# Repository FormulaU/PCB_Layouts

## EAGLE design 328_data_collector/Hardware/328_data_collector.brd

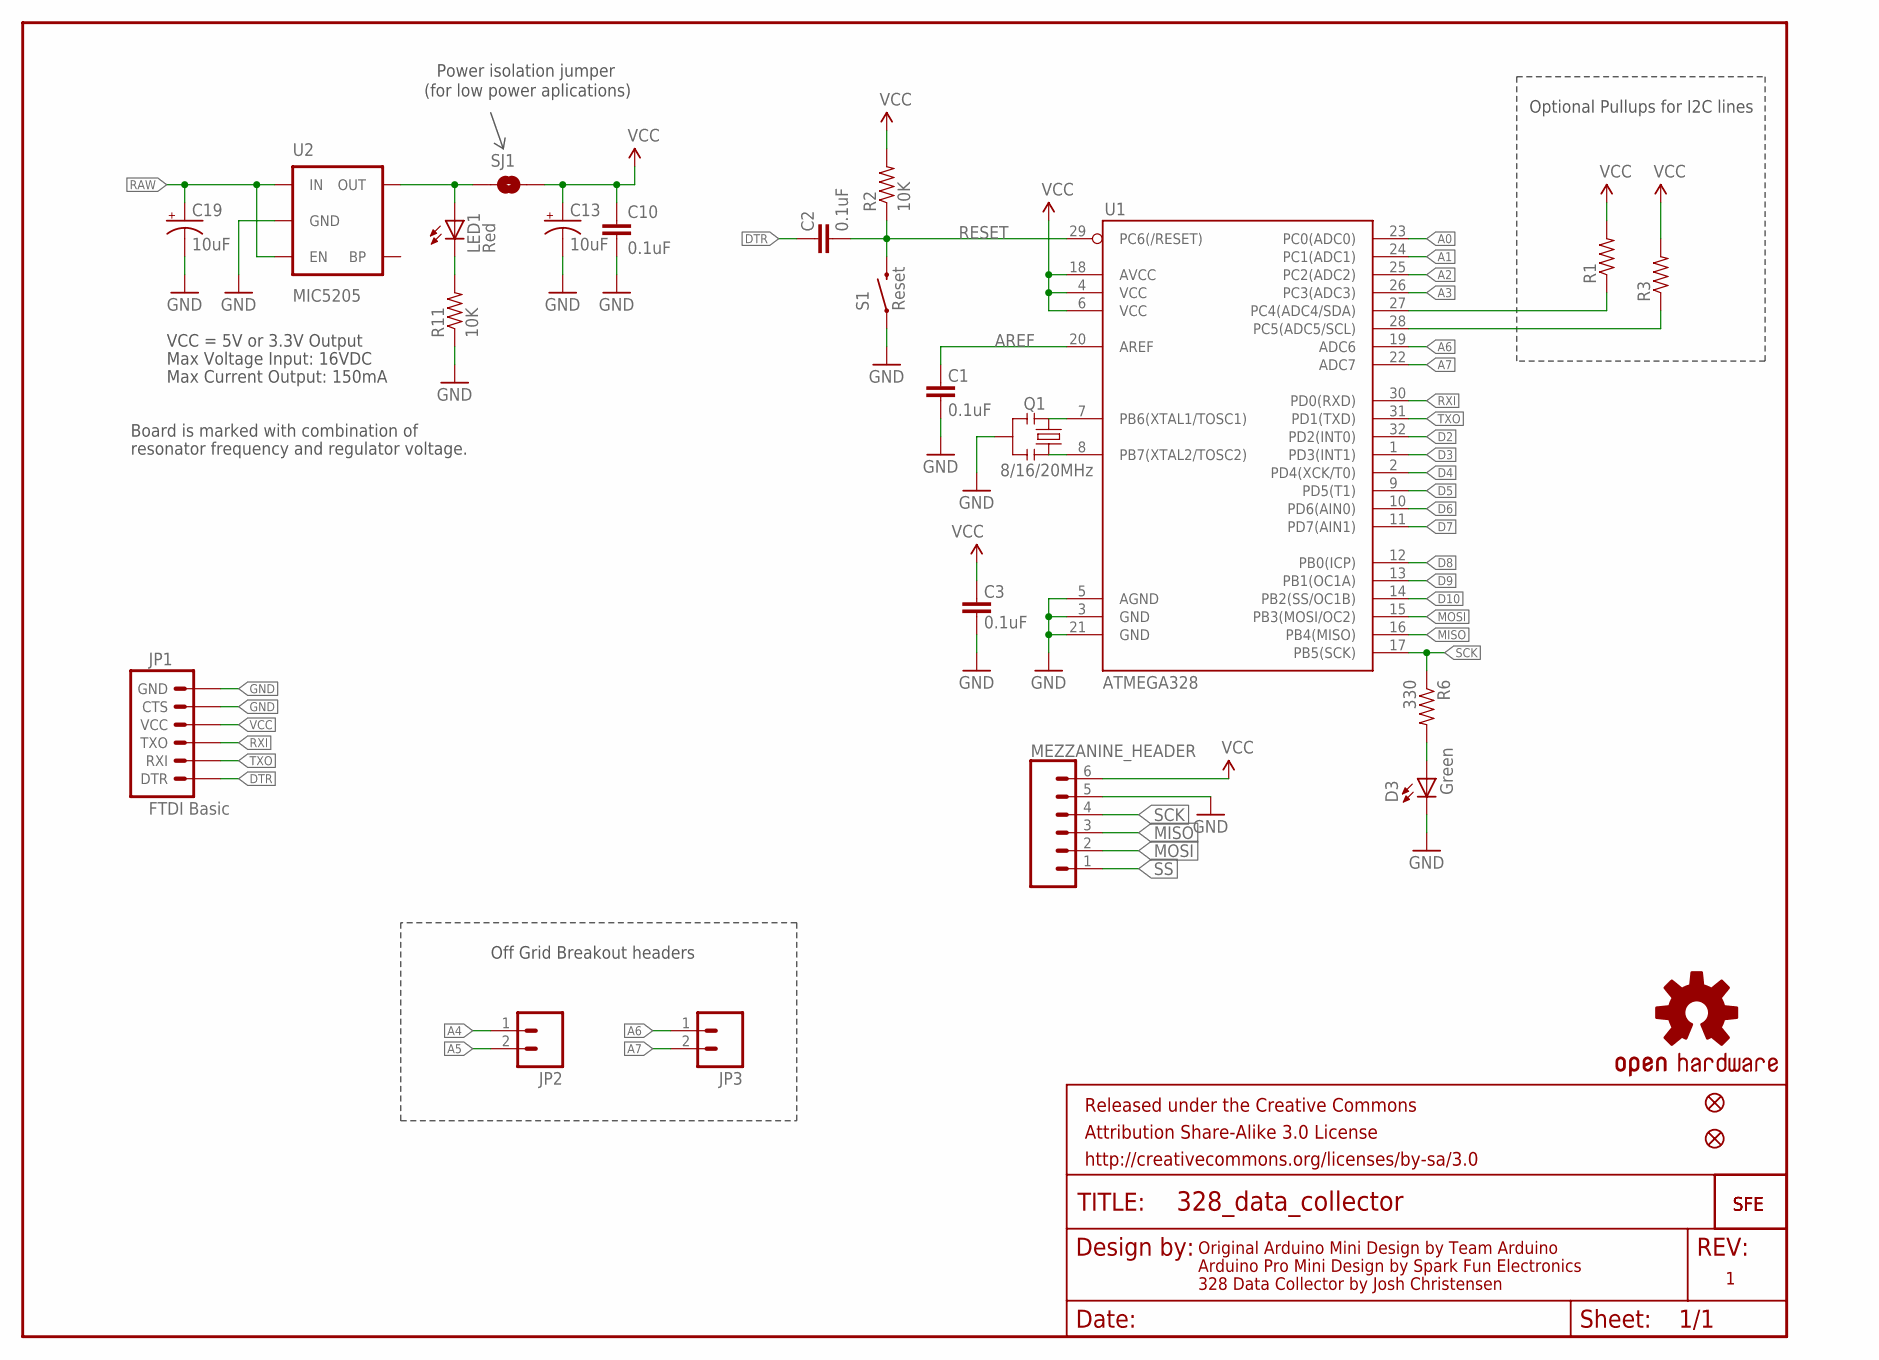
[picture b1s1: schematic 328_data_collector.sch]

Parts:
C1, C2, C3, C10: 0.1uF; 0603-CAP
C13, C19: 10uF; EIA3216
D3: Green; 0603-LED-ALT1
FRAME1: FRAME-LETTER; CREATIVE_COMMONS
JP1: FTDI Basic; 1X06
JP2, JP3: M02PTH; 1X02
JP5, JP8: FIDUCIALUFIDUCIAL; MICRO-FIDUCIAL
LED1: Red; 0603-LED-ALT1
MEZZANINE_HEADER: CONN_06SILK_FEMALE_PTH; 1X06
Q1: 8/16/20MHz; RESONATOR-SMD-1:1
R1, R3: RESISTOR0603-RES; 0603-RES
R2, R11: 10K; 0603-RES
R6: 330; 0603-RES
S1: Reset; TACTILE-SWITCH-SMD-ALT01
SJ1: SOLDERJUMPERNC; SJ_2S
U1: ATMEGA328; TQFP32-08
U2: MIC5205; SOT23-5
U$1: LOGO-SFESK; SFE-LOGO-FLAME
U$3: OSHW-LOGOS; OSHW-LOGO-S
U$11: LOGO-SFENEW; SFE-NEW-WEBLOGO

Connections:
3.3V: MEZZANINE_HEADER.6
A0: U1.23 (PC0(ADC0))
A1: U1.24 (PC1(ADC1))
A2: U1.25 (PC2(ADC2))
A3: U1.26 (PC3(ADC3))
A4: JP2.1, R1.1, U1.27 (PC4(ADC4/SDA))
A5: JP2.2, R3.1, U1.28 (PC5(ADC5/SCL))
A6: JP3.1, U1.19 (ADC6)
A7: JP3.2, U1.22 (ADC7)
AREF: C1.2, U1.20 (AREF)
D2: U1.32 (PD2(INT0))
D3: U1.1 (PD3(INT1))
D4: U1.2 (PD4(XCK/T0))
D5: U1.9 (PD5(T1))
D6: U1.10 (PD6(AIN0))
D7: U1.11 (PD7(AIN1))
D8: U1.12 (PB0(ICP))
D9: U1.13 (PB1(OC1A))
D10: U1.14 (PB2(SS/OC1B))
DTR: C2.2, JP1.1 (DTR)
GND: C1.1, C3.1, C10.2, C13.C (-), C19.C (-), D3.C, JP1.5 (CTS), JP1.6 (GND), MEZZANINE_HEADER.5, Q1.2, R11.1, S1.1, S1.2 (1), U1.3 (GND), U1.5 (AGND), U1.21 (GND), U2.2 (GND)
MISO: MEZZANINE_HEADER.3, U1.16 (PB4(MISO))
MOSI: MEZZANINE_HEADER.2, U1.15 (PB3(MOSI/OC2))
unnamed: Q1.3, U1.8 (PB7(XTAL2/TOSC2))
unnamed: Q1.1, U1.7 (PB6(XTAL1/TOSC1))
unnamed: LED1.A, SJ1.1, U2.5 (OUT)
unnamed: LED1.C, R11.2
unnamed: D3.A, R6.2
RAW: C19.A (+), U2.1 (IN), U2.3 (EN)
RESET: C2.1, R2.1, S1.3 (2), S1.4 (2), U1.29 (PC6(/RESET))
RXI: JP1.3 (TXO), U1.30 (PD0(RXD))
SCK: MEZZANINE_HEADER.4, R6.1, U1.17 (PB5(SCK))
SS: MEZZANINE_HEADER.1
TXO: JP1.2 (RXI), U1.31 (PD1(TXD))
VCC: C3.2, C10.1, C13.A (+), JP1.4 (VCC), R1.2, R2.2, R3.2, SJ1.2, U1.4 (VCC), U1.6 (VCC), U1.18 (AVCC)

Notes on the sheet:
Original Arduino Mini Design by Team Arduino
Arduino Pro Mini Design by Spark Fun Electronics
Max Voltage Input: 16VDC
Max Current Output: 150mA
Board is marked with combination of
resonator frequency and regulator voltage.
VCC = 5V or 3.3V Output
Optional Pullups for I2C lines
Off Grid Breakout headers
Power isolation jumper
(for low power aplications)
328 Data Collector by Josh Christensen

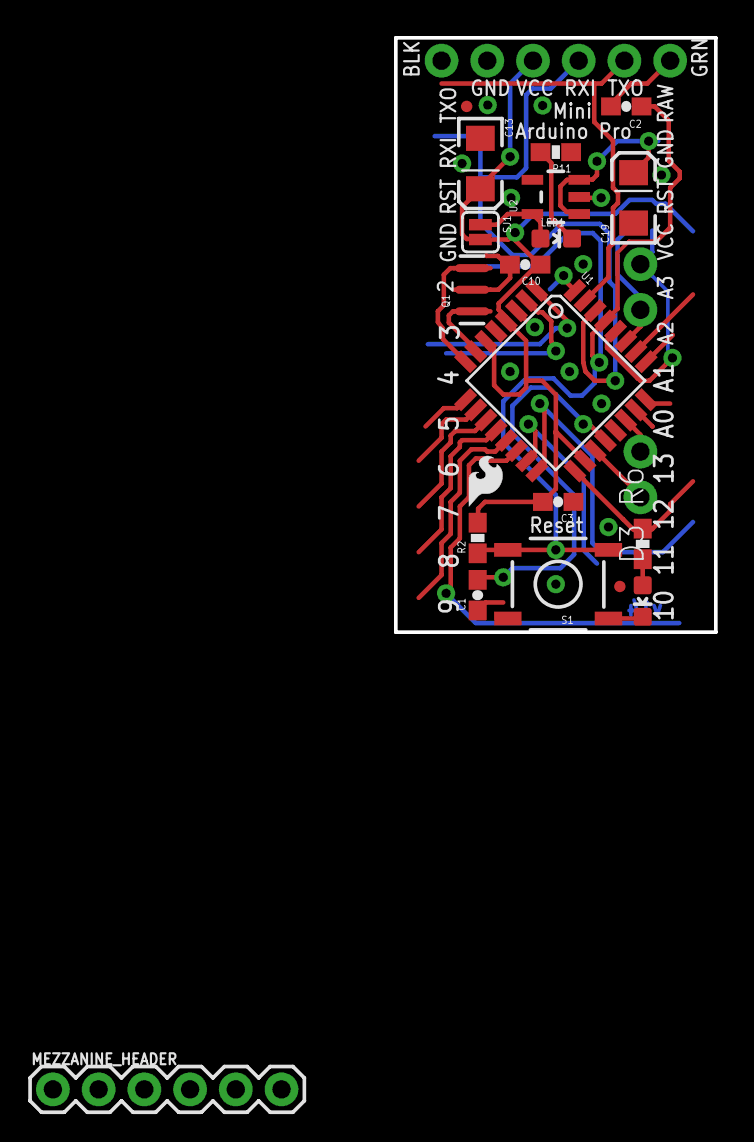
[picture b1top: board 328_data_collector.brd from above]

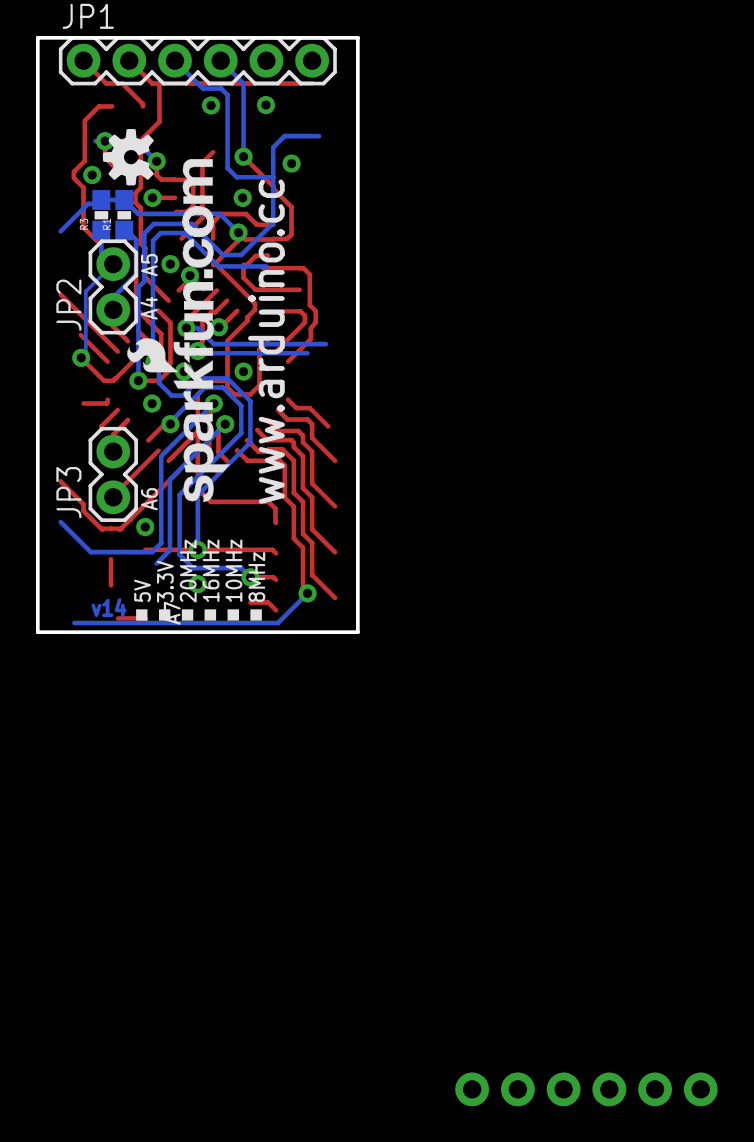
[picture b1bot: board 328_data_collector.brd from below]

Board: 2 copper layers, 17.8 x 33.0 mm, 28 parts (7 on the bottom side), 20 nets.

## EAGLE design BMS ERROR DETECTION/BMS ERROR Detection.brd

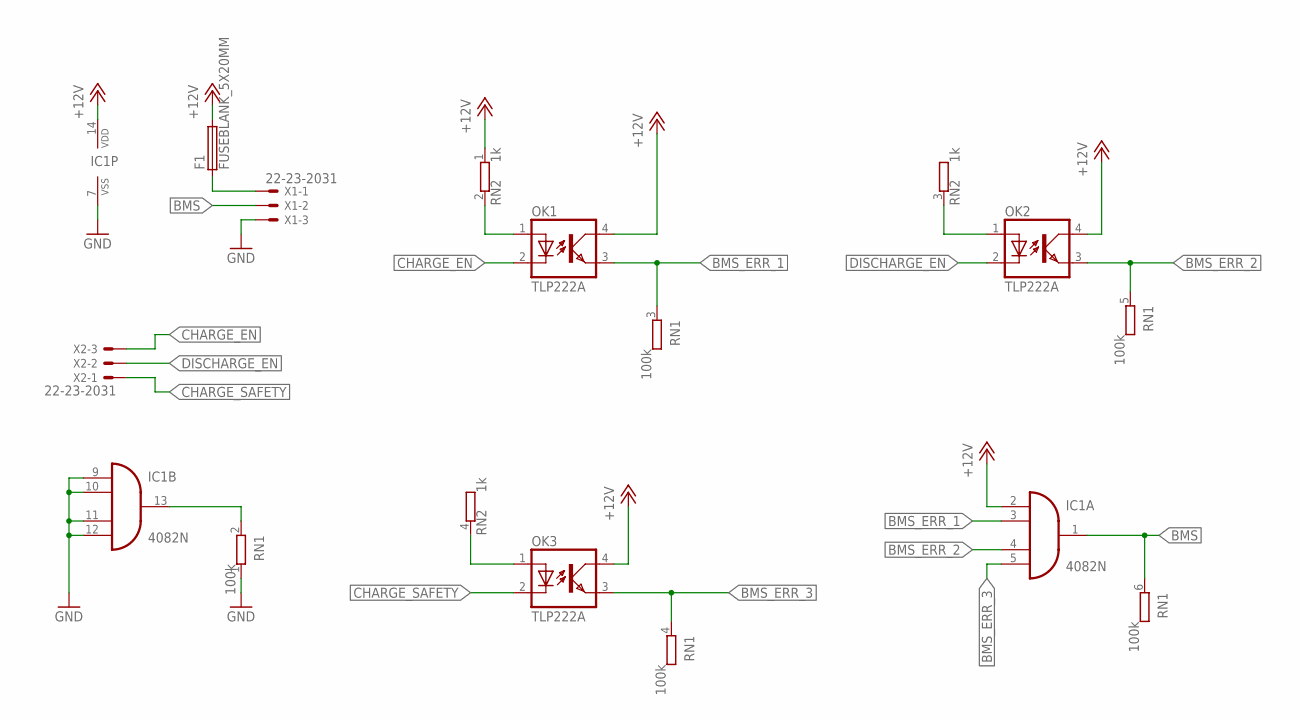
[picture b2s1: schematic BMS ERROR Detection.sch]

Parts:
F1: FUSEBLANK_5X20MM; FUSE_HOLDER_5X20MM
IC1: 4082N; DIL14
OK1, OK2, OK3: TLP222A; DIL04
RN1: 100k; SIL6
RN2: 1k; SIL4
X1, X2: 22-23-2031

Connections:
+12V: F1.2, IC1.2 (I0), IC1.14 (VDD), OK1.4 (COL), OK2.4 (COL), OK3.4 (COL), RN2.1
BMS: IC1.1 (O), RN1.6 (2), X1.2
BMS_ERR_1: IC1.3 (I1), OK1.3 (EMIT), RN1.3 (2)
BMS_ERR_2: IC1.4 (I2), OK2.3 (EMIT), RN1.5 (2)
BMS_ERR_3: IC1.5 (I3), OK3.3 (EMIT), RN1.4 (2)
CHARGE_EN: OK1.2 (C), X2.3
CHARGE_SAFETY: OK3.2 (C), X2.1
DISCHARGE_EN: OK2.2 (C), X2.2
GND: IC1.7 (VSS), IC1.9 (I0), IC1.10 (I1), IC1.11 (I2), IC1.12 (I3), RN1.1, X1.3
unnamed: IC1.13 (O), RN1.2
unnamed: OK1.1 (A), RN2.2
unnamed: OK2.1 (A), RN2.3 (2)
unnamed: OK3.1 (A), RN2.4 (2)
unnamed: F1.1, X1.1

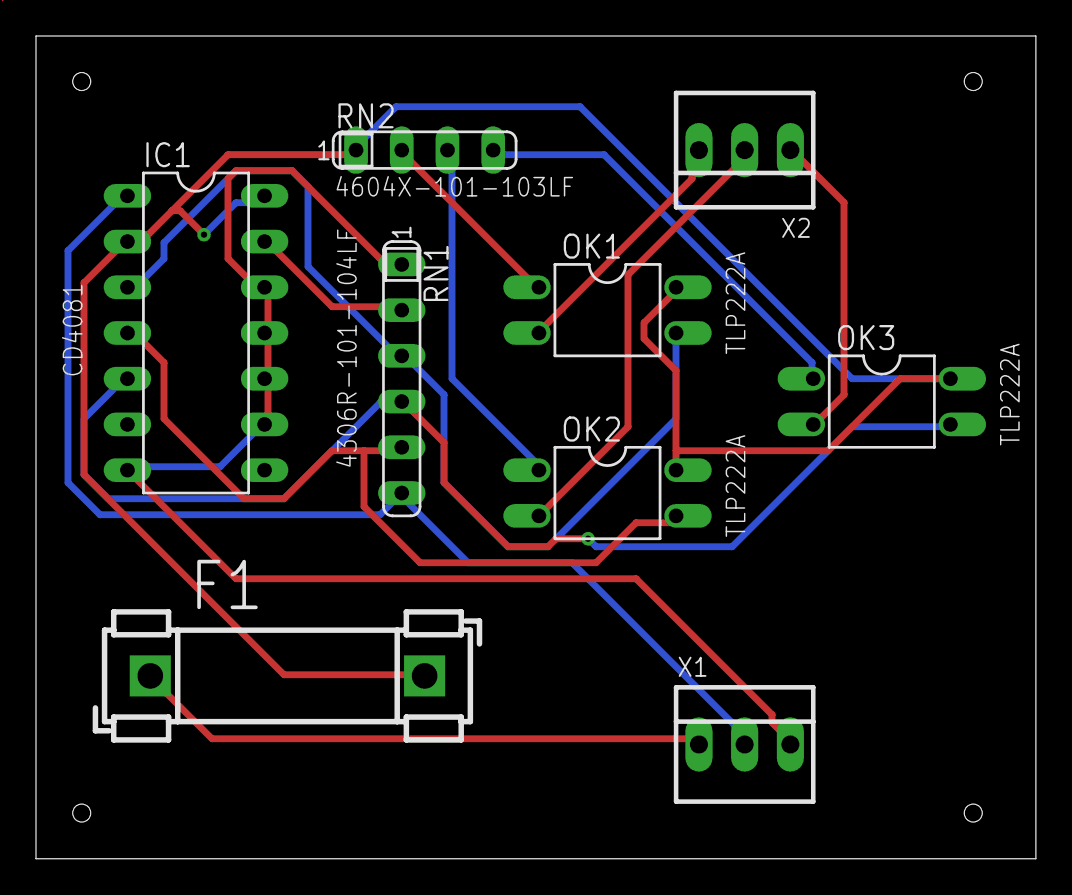
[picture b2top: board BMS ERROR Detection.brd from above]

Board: 2 copper layers, 55.5 x 45.7 mm, 9 parts (0 on the bottom side), 14 nets.

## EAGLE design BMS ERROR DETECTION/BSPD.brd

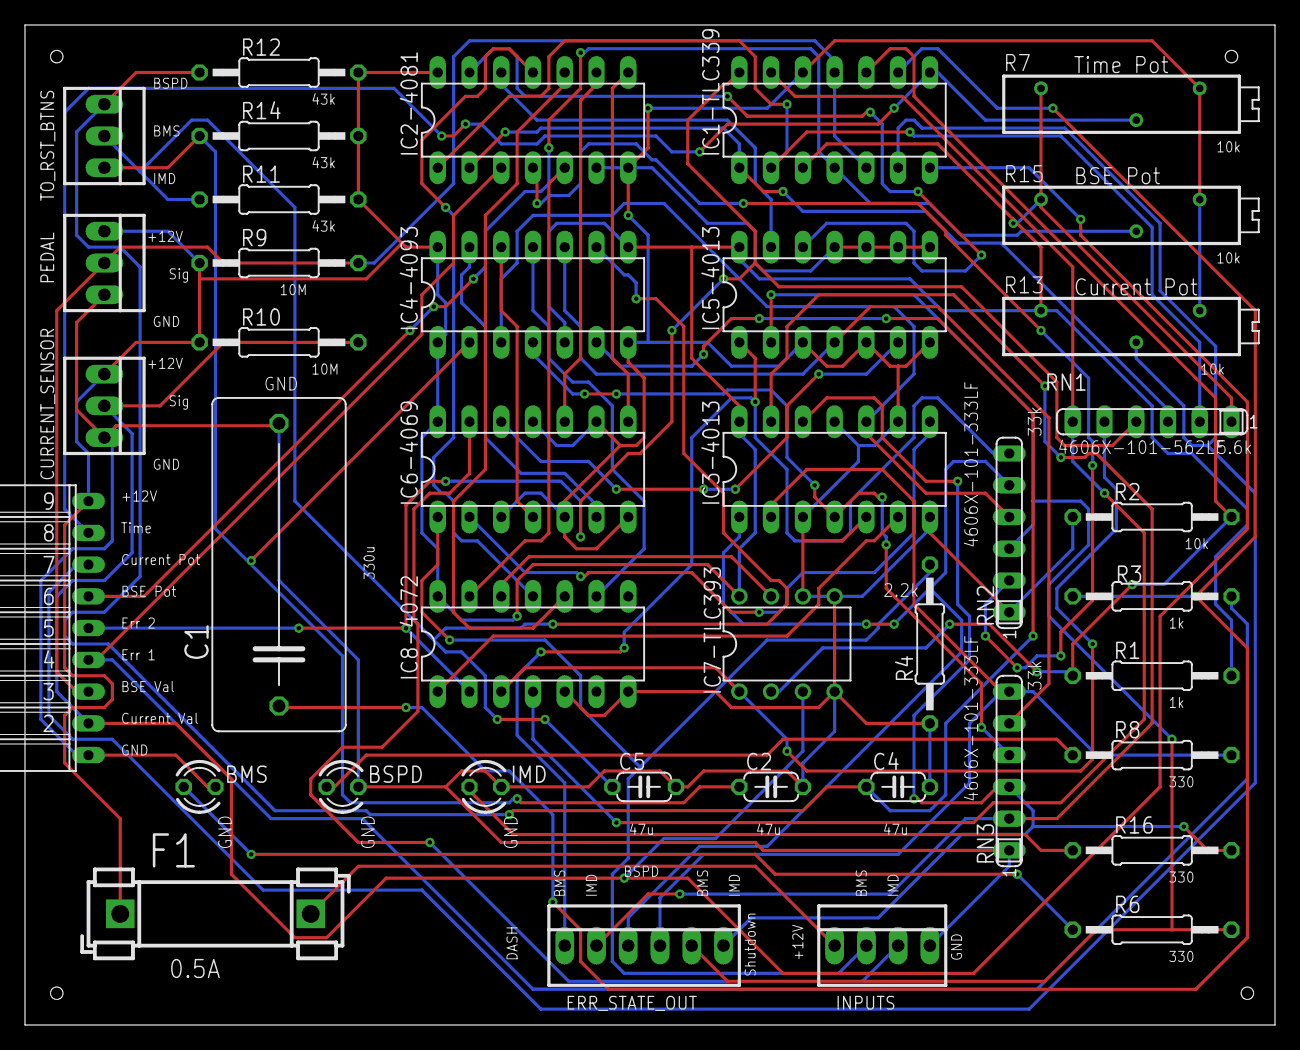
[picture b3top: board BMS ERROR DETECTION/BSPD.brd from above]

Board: 2 copper layers, 100.0 x 80.0 mm, 40 parts (0 on the bottom side), 48 nets.

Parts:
BMS: LED3; LED3MM
BSPD: LED2; LED3MM
C1: 330u; C225-108X268
C2, C4, C5: 47uF; C050-024X044
CURRENT_SENSOR: 22-23-2031
ERR_STATE_OUT: 22-23-2061
F1: FUSEBLANK_5X20MM; FUSE_HOLDER_5X20MM
IC1-TLC339: TLC339P; DIL14
IC2-4081: 4081N; DIL14
IC3-4013, IC5-4013: 4013N; DIL14
IC4-4093: 4093N; DIL14
IC6-4069: 4069N; DIL14
IC7-TLC393: TLC393P; DIL08
IC8-4072: 4072N; DIL14
IMD: LED4; LED3MM
INPUTS: 22-23-2041
PEDAL: 22-23-2031
R1, R3: 1k; 0207/12
R2: 10k; 0207/12
R4: 2.2k; 0207/12
R6, R8, R16: 330; 0207/12
R7, R13, R15: 10k; RTRIM3006P
R9, R10: 10M; 0207/12
R11, R12, R14: 43k; 0207/12
RN1: 5.1k; SIL6
RN2, RN3: 33k; SIL6
S7042-ND: FE09W
TO_RST_BTNS: 22-23-2031

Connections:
+12V: CURRENT_SENSOR.1, F1.1, IC1-TLC339.3, IC2-4081.14, IC3-4013.14, IC4-4093.1, IC4-4093.5, IC4-4093.8, IC4-4093.14, IC5-4013.14, IC6-4069.14, IC7-TLC393.8, IC8-4072.14, PEDAL.1, R1.2, R7.1, R9.1, R10.1, R11.2, R12.2, R13.1, R14.2, R15.1, RN1.1, S7042-ND.9
BMS: IC6-4069.13, INPUTS.3
BMS_DASH: ERR_STATE_OUT.1, IC5-4013.1, RN2.6
BMS_ERR: ERR_STATE_OUT.5, IC5-4013.2, R6.2, RN2.3
BMS_RST: IC4-4093.10, IC5-4013.4, RN3.5
BSE: IC1-TLC339.5, IC1-TLC339.11, PEDAL.2, R9.2, S7042-ND.3
BSE_POT: IC1-TLC339.4, R15.2, S7042-ND.6
BSE_UNPLUGGED: IC1-TLC339.13, IC8-4072.4, RN1.6
BSPD_DASH: ERR_STATE_OUT.3, IC3-4013.1, RN2.5
BSPD_ERR: ERR_STATE_OUT.4, IC3-4013.2, R8.2, RN3.6
BSPD_RST: IC3-4013.4, IC4-4093.4, RN3.4
CURRENT_POT: IC1-TLC339.6, R13.2, S7042-ND.7
CURRENT_SENSOR: CURRENT_SENSOR.2, IC1-TLC339.7, IC7-TLC393.3, R10.2, S7042-ND.2
CURR_UNPLUGGED: IC7-TLC393.1, IC8-4072.3, RN1.5
ERROR_1: IC2-4081.3, R3.1, S7042-ND.4
ERROR_2: IC1-TLC339.14, IC8-4072.2, RN1.4, S7042-ND.5
ERROR_3: IC3-4013.6, IC8-4072.1
ESO_BMS_RST: C5.1, IC4-4093.9, R11.1, TO_RST_BTNS.2
ESO_BSPD_RST: C4.1, IC4-4093.6, R12.1, TO_RST_BTNS.1
ESO_IMD_RST: C2.1, IC4-4093.2, R14.1, TO_RST_BTNS.3
GND: BMS.K, BSPD.K, C1.2, C2.2, C4.2, C5.2, CURRENT_SENSOR.3, IC1-TLC339.12, IC2-4081.6, IC2-4081.7, IC3-4013.3, IC3-4013.5, IC3-4013.7, IC3-4013.9, IC3-4013.11, IC4-4093.7, IC5-4013.3, IC5-4013.5, IC5-4013.7, IC5-4013.8, IC5-4013.9, IC5-4013.10, IC5-4013.11, IC6-4069.3, IC6-4069.5, IC6-4069.7, IC6-4069.9, IC6-4069.11, IC7-TLC393.4, IC7-TLC393.5, IC7-TLC393.6, IC8-4072.5, IC8-4072.7, IMD.K, INPUTS.4, PEDAL.3, R2.1, R4.1, R7.3, R13.3, R15.3, RN2.1, RN3.1, S7042-ND.1
IMD: IC6-4069.1, INPUTS.2, R4.2
IMD_DASH: ERR_STATE_OUT.2, IC3-4013.13, RN3.2
IMD_ERR: ERR_STATE_OUT.6, IC3-4013.12, R16.2, RN3.3
IMD_RST: IC3-4013.10, IC4-4093.3, RN2.4
unnamed: IC1-TLC339.2, IC2-4081.1, RN1.2
unnamed: IC1-TLC339.1, IC2-4081.2, RN1.3
unnamed: F1.2, INPUTS.1
unnamed: IC3-4013.8, IC6-4069.2
unnamed: C1.1, IC1-TLC339.9, R3.2
unnamed: IC7-TLC393.7, IC8-4072.12
unnamed: IC4-4093.11, IC8-4072.9
unnamed: BMS.A, R6.1
unnamed: IC4-4093.12, IC6-4069.4
unnamed: IC2-4081.10, IC8-4072.10
unnamed: IC2-4081.11, IC8-4072.11
unnamed: IC4-4093.13, IC6-4069.6
unnamed: IC5-4013.6, IC6-4069.12
unnamed: IMD.A, R16.1
unnamed: IC2-4081.9, IC6-4069.10
unnamed: IC2-4081.8, IC6-4069.8
unnamed: IC2-4081.5, IC8-4072.13
unnamed: BSPD.A, R8.1
unnamed: IC2-4081.12, IC5-4013.13
unnamed: IC2-4081.13, IC5-4013.12
unnamed: IC2-4081.4, RN2.2
TIMED_POT: IC1-TLC339.8, R7.2, S7042-ND.8
UNPLUG: IC1-TLC339.10, IC7-TLC393.2, R1.1, R2.2

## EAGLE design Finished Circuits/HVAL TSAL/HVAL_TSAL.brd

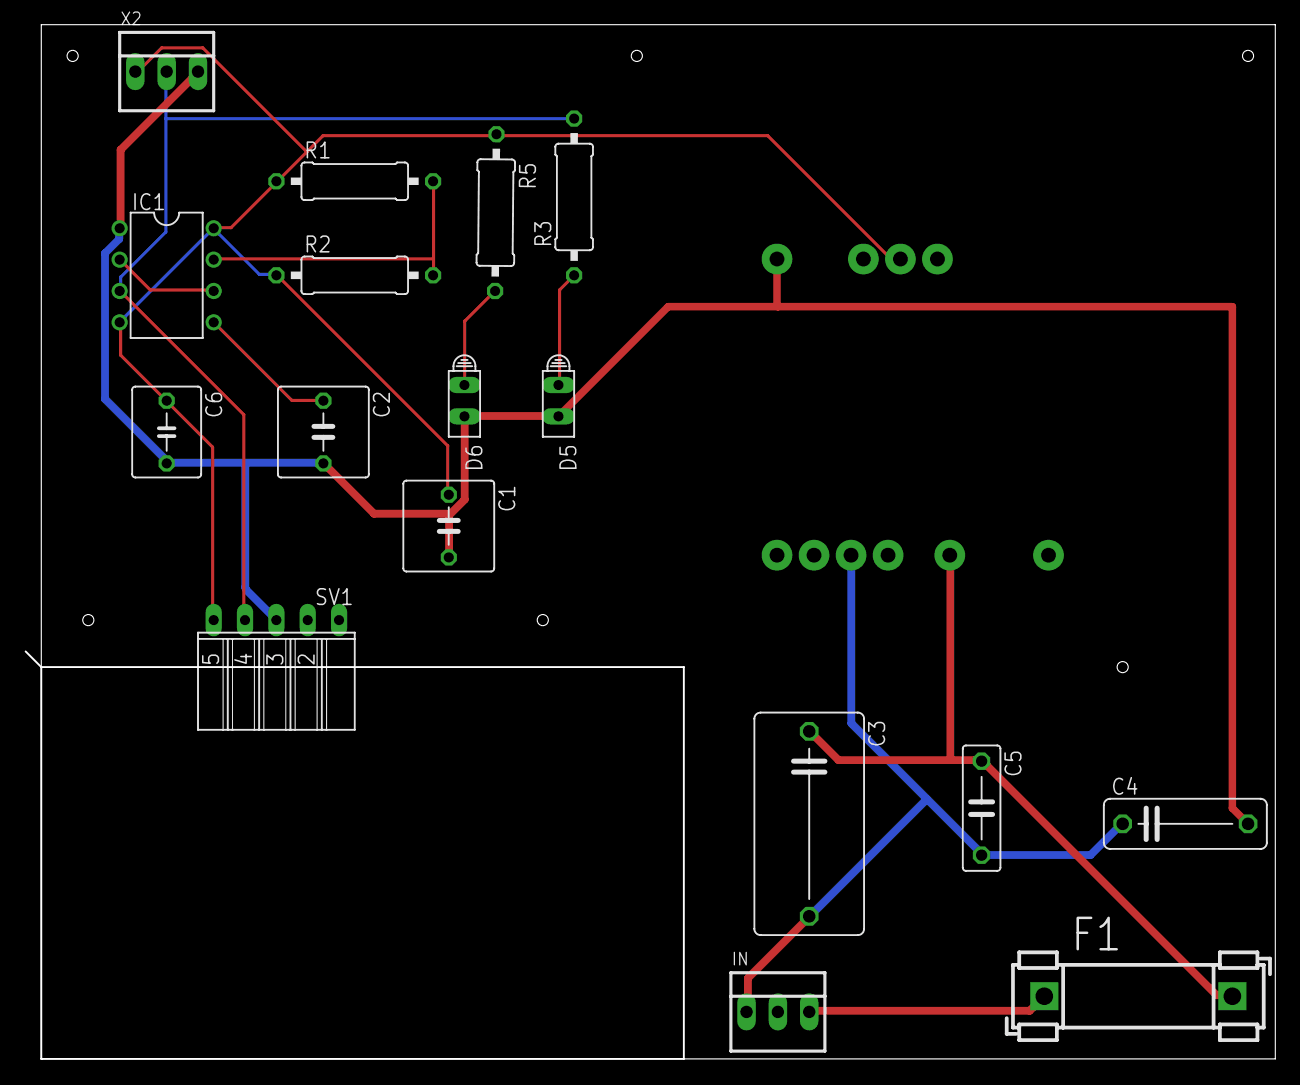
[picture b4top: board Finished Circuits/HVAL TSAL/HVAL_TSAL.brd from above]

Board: 2 copper layers, 101.3 x 83.8 mm, 18 parts (0 on the bottom side), 11 nets.

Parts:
C1: 0.47u; C050-075X075
C2: 0.15u; C050-075X075
C3: C150-091X182
C4: C102-043X133
C5: C075-032X103
C6: C050-055X075
D5, D6: HLMP6
F1: FUSEBLANK_5X20MM; FUSE_HOLDER_5X20MM
IC1: LM555N; DIL08
IN: 22-23-2031
R1: 66k; 0309/12
R2: 350k; 0309/12
R3, R5: 100; 0309/12
SV1: FE05W
U$1: EPM1205SJ
X2: 22-23-2031

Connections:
HVAL_IN: D5.A, R3.1
LOW_SIDE_NEG: C1.2, C2.2, C4.2, C6.2, D5.K, D6.K, IC1.1, SV1.3, U$1.7, X2.3
LOW_SIDE_POS: C1.1, C6.1, IC1.4, IC1.8, R1.1, R2.1, R5.1, SV1.5, U$1.5, X2.1
unnamed: C3.1, C5.1, F1.2, U$1.12
unnamed: C3.2, C4.1, C5.2, IN.1, U$1.10
unnamed: IC1.7, R1.2, R2.2
unnamed: C2.1, IC1.5
unnamed: IC1.2, IC1.6
unnamed: F1.1, IN.3
TSAL_IN: D6.A, R5.2
TSAL_OUT: IC1.3, R3.2, SV1.4, X2.2

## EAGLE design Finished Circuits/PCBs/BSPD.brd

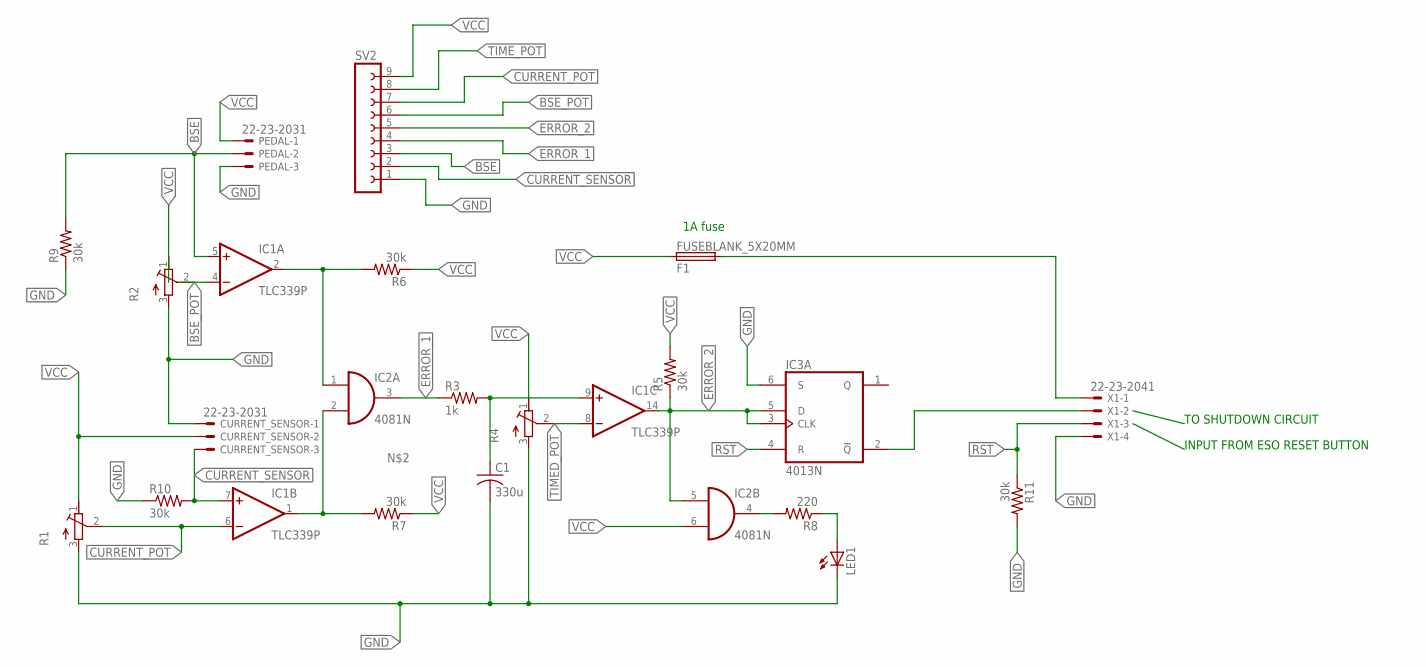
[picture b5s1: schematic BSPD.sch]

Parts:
C1: 330u; C225-108X268
CURRENT_SENSOR: 22-23-2031
F1: FUSEBLANK_5X20MM; FUSE_HOLDER_5X20MM
IC1: TLC339P; DIL14
IC2: 4081N; DIL14
IC3: 4013N; DIL14
LED1: LED5MM
PEDAL: 22-23-2031
R1, R4: R-TRIMM3006P; RTRIM3006P
R2: R-TRIMM43P; RTRIM43P
R3: 1k; 0207/12
R5, R6, R7, R9, R10, R11: 30k; 0207/12
R8: 220; 0207/12
SV2: FE09W
X1: 22-23-2041

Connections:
BSE: IC1.5 (+IN), PEDAL.2, R9.2, SV2.3
BSE_POT: IC1.4 (-IN), R2.2 (S), SV2.6
CURRENT_POT: IC1.6 (-IN), R1.2 (S), SV2.7
CURRENT_SENSOR: CURRENT_SENSOR.3, IC1.7 (+IN), R10.2, SV2.2
ERROR_1: IC2.3 (O), R3.1, SV2.4
ERROR_2: IC1.14 (OUT), IC2.5 (I0), IC3.3 (CLK), IC3.5 (D), R5.1, SV2.5
GND: C1.2, CURRENT_SENSOR.1, IC3.6 (S), LED1.K (C), PEDAL.3, R1.3 (A), R2.3 (A), R4.3 (A), R9.1, R10.1, R11.2, SV2.1, X1.4
unnamed: IC1.2 (OUT), IC2.1 (I0), R6.2
unnamed: IC1.1 (OUT), IC2.2 (I1), R7.2
unnamed: IC3.2 (!Q), X1.2
unnamed: F1.2, X1.1
unnamed: C1.1, IC1.9 (+IN), R3.2
unnamed: IC2.4 (O), R8.2
unnamed: LED1.A, R8.1
RST: IC3.4 (R), R11.1, X1.3
TIMED_POT: IC1.8 (-IN), R4.2 (S)
TIME_POT: SV2.8
V+: IC1.3 (V+)
V-: IC1.12 (V-)
VCC: CURRENT_SENSOR.2, F1.1, IC2.6 (I1), PEDAL.1, R1.1 (E), R2.1 (E), R4.1 (E), R5.2, R6.1, R7.1, SV2.9
VDD: IC2.14 (VDD), IC3.14 (VDD)
VSS: IC2.7 (VSS), IC3.7 (VSS)

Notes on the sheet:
1A fuse
TO SHUTDOWN CIRCUIT
INPUT FROM ESO RESET BUTTON

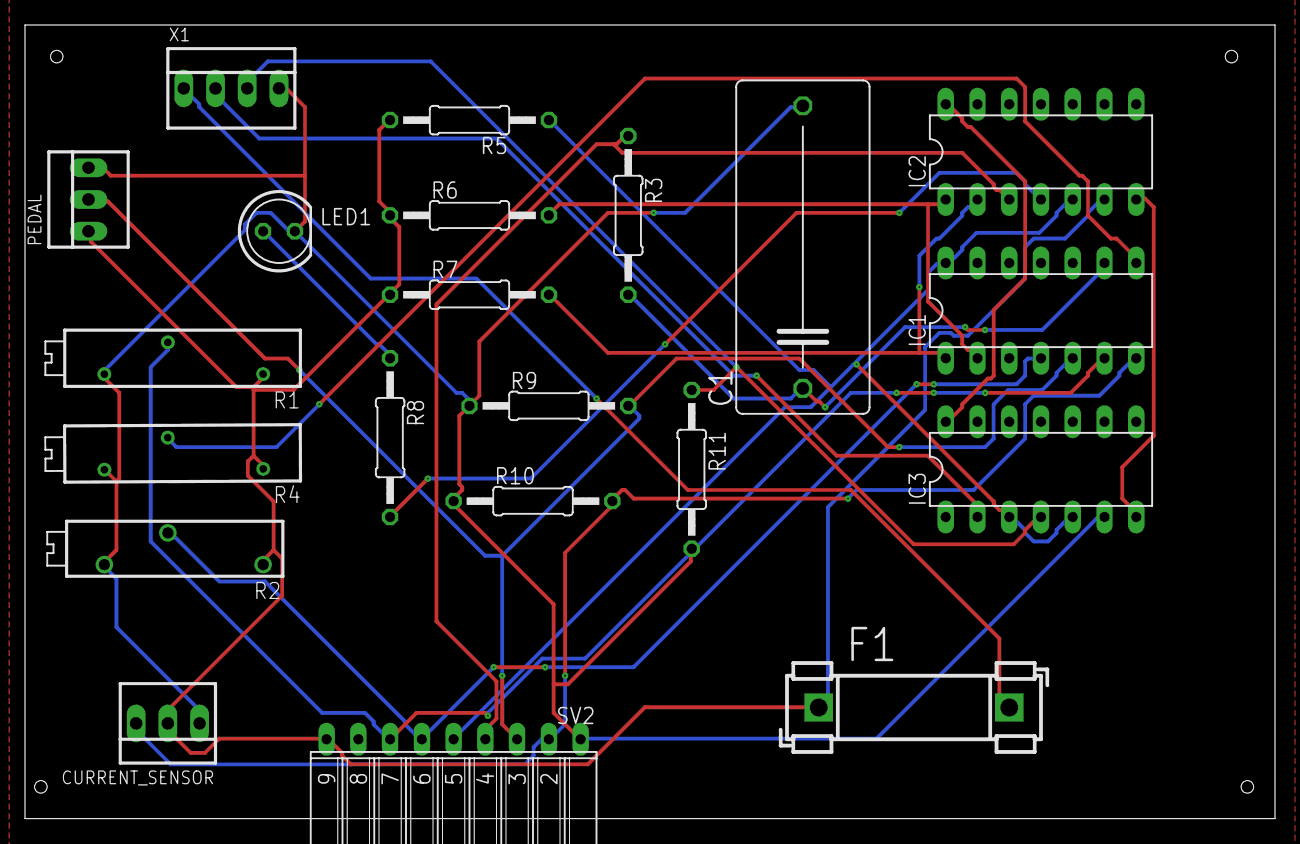
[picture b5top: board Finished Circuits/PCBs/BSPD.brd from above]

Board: 2 copper layers, 100.0 x 63.5 mm, 21 parts (0 on the bottom side), 19 nets.

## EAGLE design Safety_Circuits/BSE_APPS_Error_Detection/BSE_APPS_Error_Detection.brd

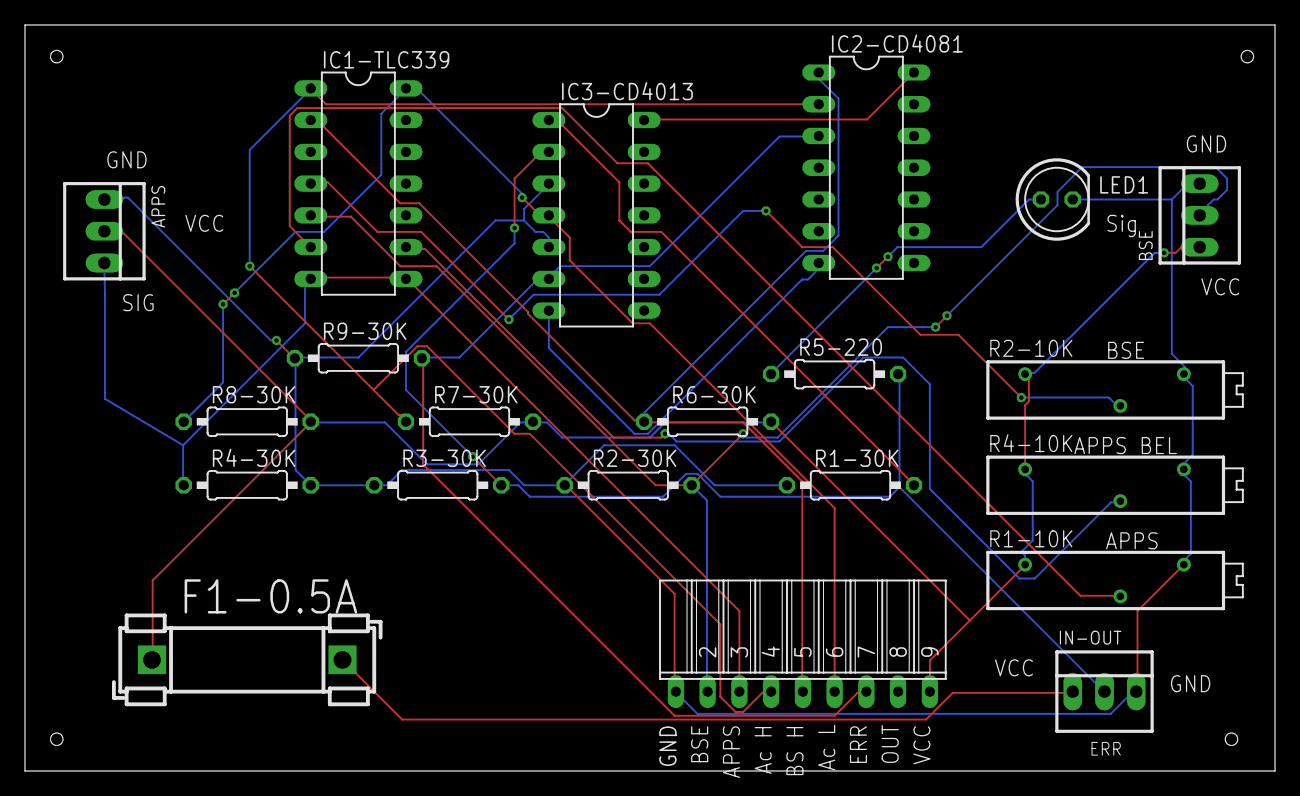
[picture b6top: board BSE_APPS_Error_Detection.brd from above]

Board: 2 copper layers, 100.0 x 59.7 mm, 21 parts (0 on the bottom side), 17 nets.

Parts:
APPS: 22-23-2031
BSE: 22-23-2031
F1-0.5A: FUSEBLANK_5X20MM; FUSE_HOLDER_5X20MM
GND: FE09W
IC1-TLC339: TLC339P; DIL14
IC2-CD4081: 4081N; DIL14
IC3-CD4013: 4013N; DIL14
IN-OUT: 22-23-2031
LED1: LED5MM
R1-10K, R2-10K, R4-10K: RTRIM3006P
R1-30K, R2-30K, R3-30K, R4-30K, R6-30K, R7-30K, R8-30K, R9-30K: 30k; 0207/10
R5-220: 220; 0207/10

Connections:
APPS_ACTUATED: GND.6, IC1-TLC339.14, IC3-CD4013.4, R8-30K.1
APPS_HIGH: GND.4, IC1-TLC339.1, IC2-CD4081.2, R7-30K.1
APPS_SIGNAL: APPS.3, GND.3, IC1-TLC339.7, IC1-TLC339.8, R4-30K.1
BSE_HIGH: GND.5, IC1-TLC339.2, IC2-CD4081.1, R6-30K.1
BSE_SIGNAL: BSE.2, GND.2, IC1-TLC339.5, R2-30K.2
ERROR: GND.7, IC2-CD4081.3, IC3-CD4013.6, R9-30K.2
GND: APPS.1, BSE.3, GND.1, IC3-CD4013.3, IC3-CD4013.5, IN-OUT.3, LED1.K, R1-10K.3, R1-30K.1, R2-10K.3, R2-30K.1, R3-30K.1, R4-10K.3, R4-30K.2, R9-30K.1
LATCHED: IC3-CD4013.2, IN-OUT.2, R3-30K.2, R5-220.2
unnamed: IC1-TLC339.9, R4-10K.2
unnamed: IC1-TLC339.4, R2-10K.2
unnamed: IC3-CD4013.1, R1-30K.2
unnamed: F1-0.5A.2, IN-OUT.1
unnamed: LED1.A, R5-220.1
unnamed: IC1-TLC339.6, R1-10K.2
VCC: APPS.2, BSE.1, F1-0.5A.1, GND.9, R1-10K.1, R2-10K.1, R4-10K.1, R6-30K.2, R7-30K.2, R8-30K.2
VDD: IC2-CD4081.14, IC3-CD4013.14
VSS: IC2-CD4081.7, IC3-CD4013.7

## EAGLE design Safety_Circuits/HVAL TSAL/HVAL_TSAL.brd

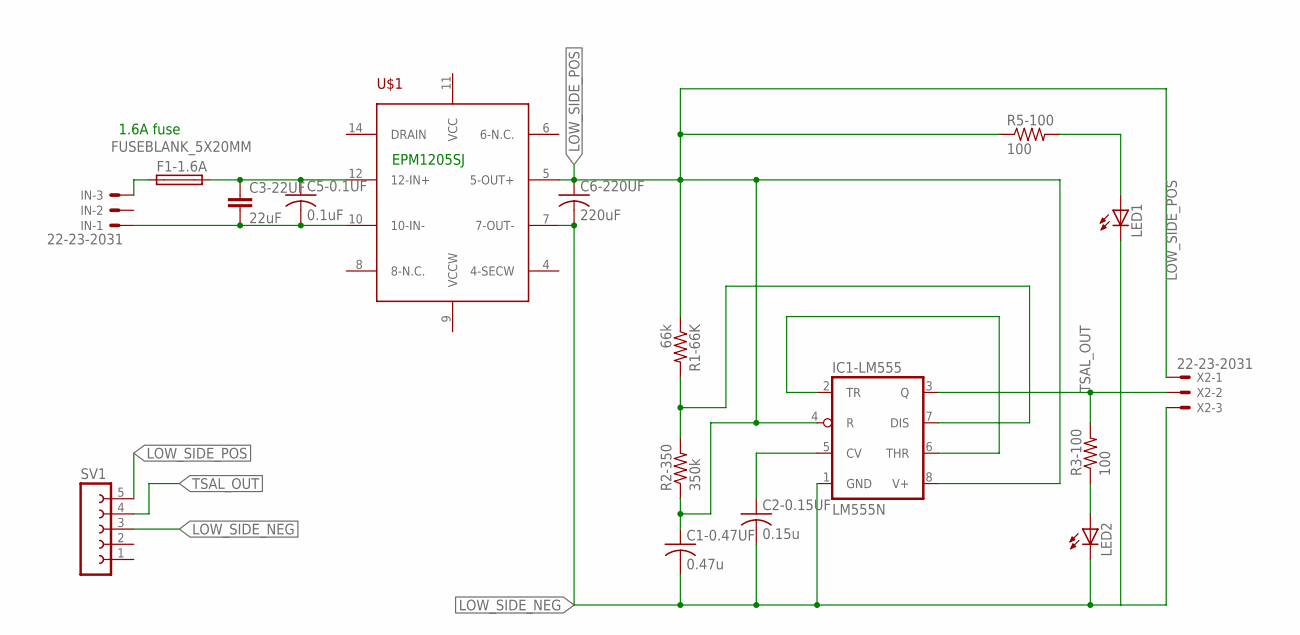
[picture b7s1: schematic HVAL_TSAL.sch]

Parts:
C1-0.47UF: 0.47u; C050-075X075
C2-0.15UF: 0.15u; C050-075X075
C3-22UF: 22uF; C150-091X182
C5-0.1UF: 0.1uF; C075-032X103
C6-220UF: 220uF; C050-055X075
F1-1.6A: FUSEBLANK_5X20MM; FUSE_HOLDER_5X20MM
IC1-LM555: LM555N; DIL08
IN: 22-23-2031
LED1, LED2: LED3MM
R1-66K: 66k; 0309/12
R2-350: 350k; 0309/12
R3-100, R5-100: 100; 0309/12
SV1: FE05W
U$1: EPM1205SJ
X2: 22-23-2031

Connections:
HVAL_IN: LED2.A, R3-100.1
LOW_SIDE_NEG: C1-0.47UF.2, C2-0.15UF.2, C6-220UF.2, IC1-LM555.1 (GND), LED1.K (C), LED2.K (C), SV1.3, U$1.7 (7-OUT-), X2.3
LOW_SIDE_POS: C1-0.47UF.1, C6-220UF.1, IC1-LM555.4 (R), IC1-LM555.8 (V+), R1-66K.1, R2-350.1, R5-100.1, SV1.5, U$1.5 (5-OUT+), X2.1
unnamed: C3-22UF.1, C5-0.1UF.1, F1-1.6A.2, U$1.12 (12-IN+)
unnamed: C3-22UF.2, C5-0.1UF.2, IN.1, U$1.10 (10-IN-)
unnamed: IC1-LM555.7 (DIS), R1-66K.2, R2-350.2
unnamed: C2-0.15UF.1, IC1-LM555.5 (CV)
unnamed: IC1-LM555.2 (TR), IC1-LM555.6 (THR)
unnamed: F1-1.6A.1, IN.3
TSAL_IN: LED1.A, R5-100.2
TSAL_OUT: IC1-LM555.3 (Q), R3-100.2, SV1.4, X2.2

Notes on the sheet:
EPM1205SJ
1.6A fuse

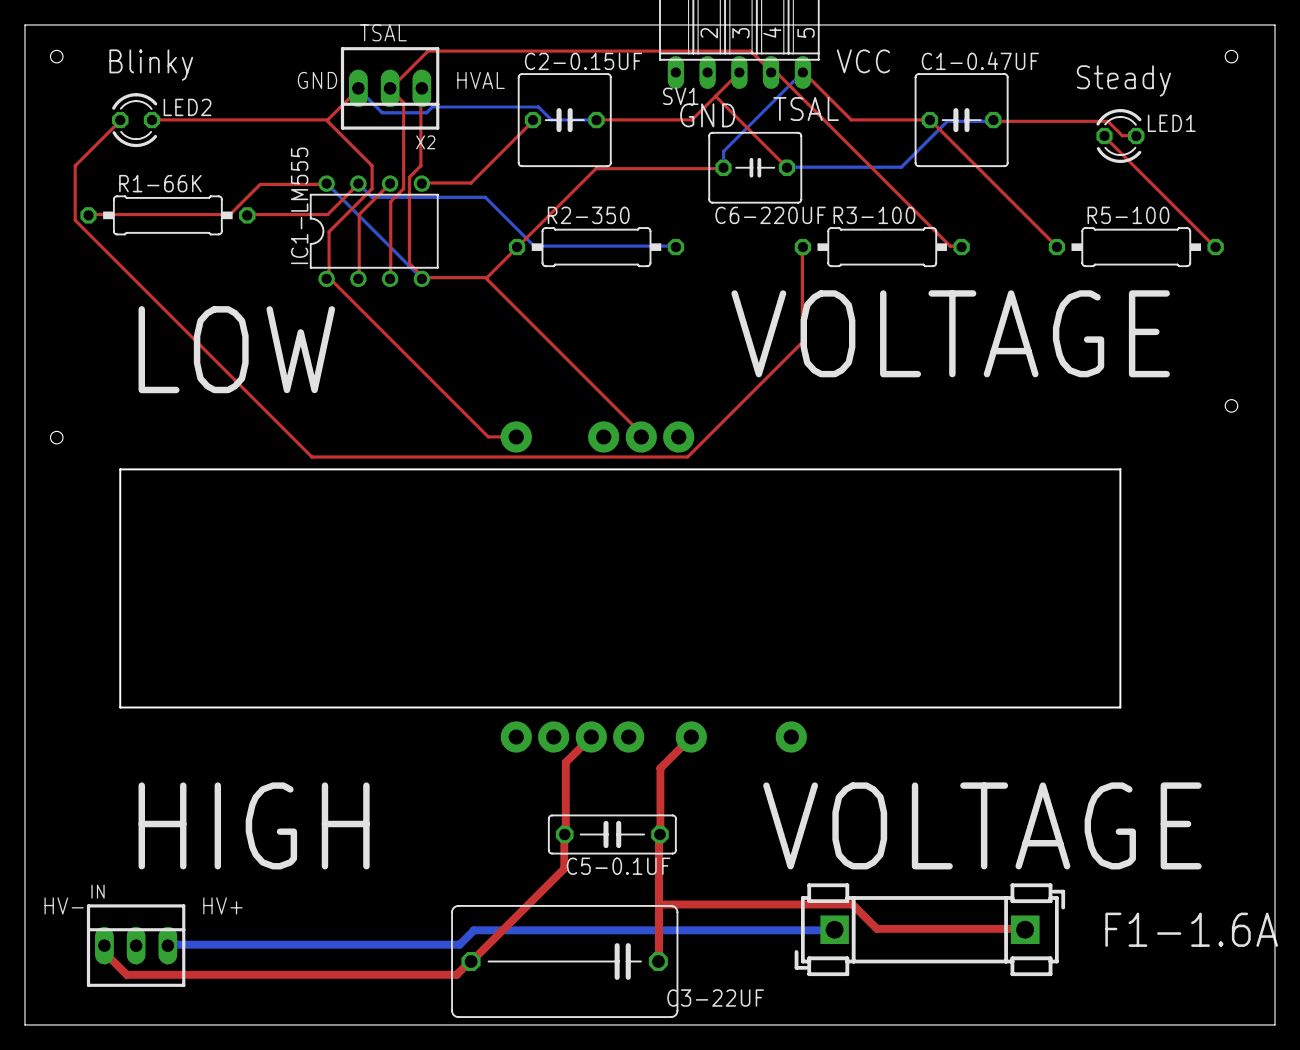
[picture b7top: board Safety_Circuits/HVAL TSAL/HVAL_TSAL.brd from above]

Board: 2 copper layers, 100.0 x 80.0 mm, 17 parts (0 on the bottom side), 11 nets.

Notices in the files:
parts and their libraries:
SparkFun-Aesthetics: Licensing: CC v3.0 Share-Alike You are welcome to use this library for commercial purposes.
SparkFun-Aesthetics: Released under the Creative Commons Attribution Share-Alike 3.0 License
SparkFun-Aesthetics: http://creativecommons.org/licenses/by-sa/3.0
